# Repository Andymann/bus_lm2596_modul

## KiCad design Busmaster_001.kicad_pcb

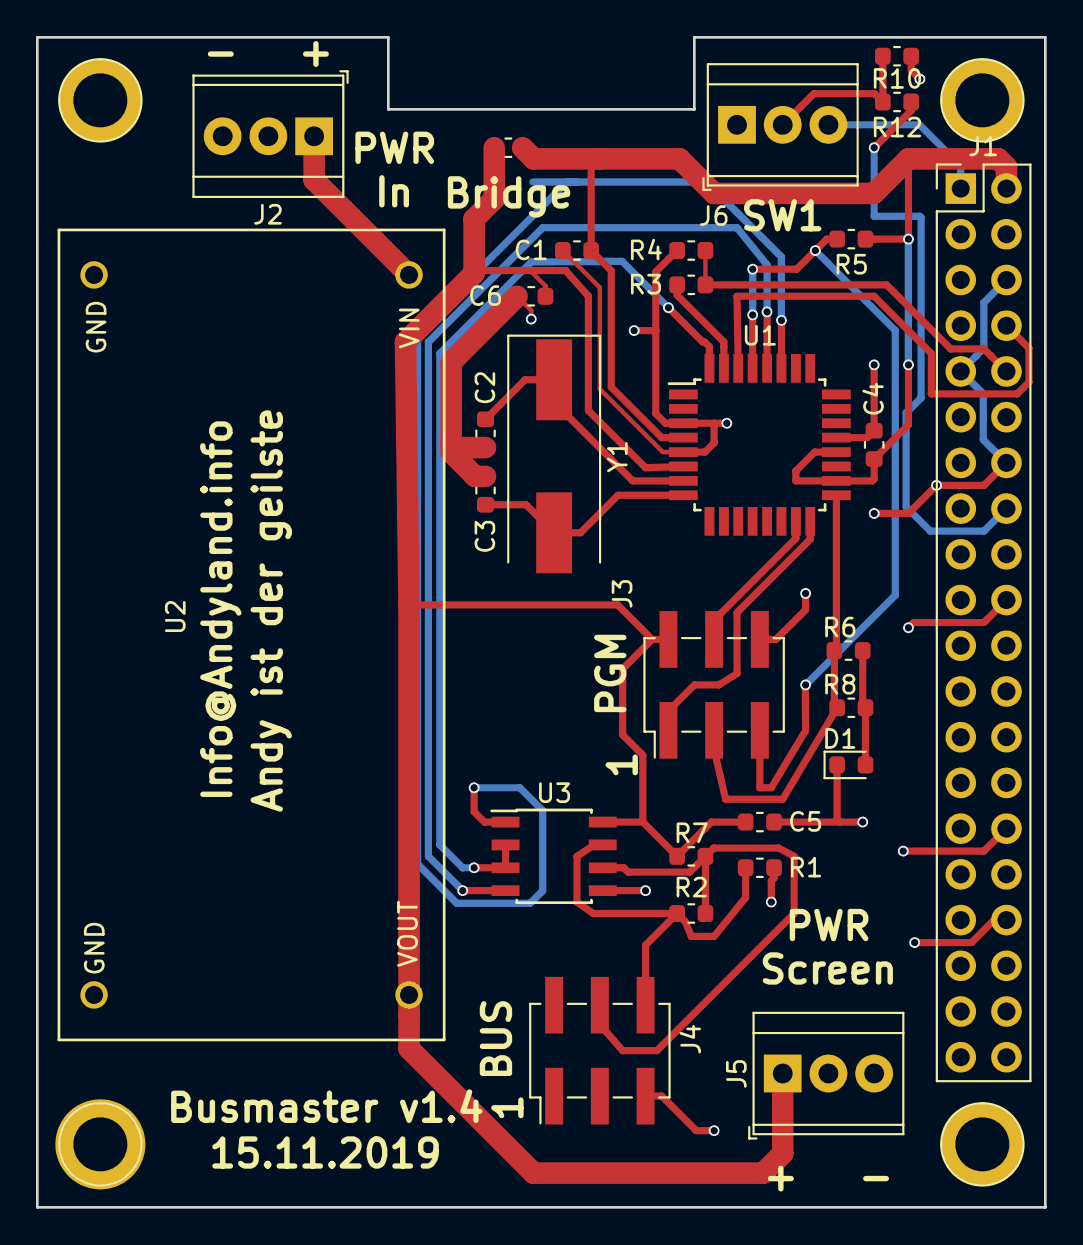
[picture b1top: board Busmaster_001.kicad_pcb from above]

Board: 2 copper layers, 56.0 x 65.0 mm, 28 parts (0 on the bottom side), 21 nets.

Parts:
C1: 100µF; C_0603_1608Metric
C2, C3: 22pF; C_0603_1608Metric
C4, C5, C6: 100nF; C_0603_1608Metric
D1: LED; LED_0603_1608Metric
J1: Conn_RPI; PinHeader_2x20_P2.54mm_Vertical
J2, J6: Conn_01x03_Female; TerminalBlock_TE_282834-3_1x03_P2.54mm_Horizontal
J3: ICSP; PinHeader_2x03_P2.54mm_Vertical_SMD
J4: CONN_BUS; PinHeader_2x03_P2.54mm_Vertical_SMD
J5: Conn_Screen; TerminalBlock_TE_282834-3_1x03_P2.54mm_Horizontal
R1, R6, R7, R8: 470; R_0603_1608Metric
R2: 100; R_0603_1608Metric
R3: 2k2; R_0603_1608Metric
R4: 3k3; R_0603_1608Metric
R5: 10k; R_0603_1608Metric
R9: 0; R_0603_1608Metric
R10: 10K; R_0603_1608Metric
R12: 1K; R_0603_1608Metric
U1: ATmega328P-AU; TQFP-32_7x7mm_P0.8mm
U2: LM2596_Module
U3: MAX485E; SOIC-8_3.9x4.9mm_P1.27mm
Y1: Crystal; Crystal_SMD_HC49-SD

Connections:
+3V3: J1.1, J6.3
+5V: C1.1, C4.2, C5.2, C6.2, J1.2, J3.2, J5.1, R5.1, R7.2, R9.1, R9.2, U1.4, U1.6, U1.18, U1.20, U2.4, U3.8
+12V: J2.1, U2.1
D2: U1.32, U3.2, U3.3
GND: C1.2, C2.1, C3.1, C4.1, C5.1, C6.1, D1.1, J1.6, J1.9, J1.14, J1.20, J1.25, J1.30, J1.34, J1.39, J2.3, J3.6, J4.5, J5.3, J6.1, R1.1, R4.2, R10.2, U1.3, U1.5, U1.21, U2.2, U2.3, U3.5
MISO: J3.1, U1.16
MOSI: J3.4, U1.15
unnamed: C2.2, U1.7, Y1.1
unnamed: C3.2, U1.8, Y1.2
unnamed: D1.2, R6.1, R8.1
unnamed: J6.2, R10.1, R12.2
unnamed: R3.1, U1.31
RESET: J3.5, R5.2, U1.29
RPI_Rx: J1.10, R3.2, R4.1
RPI_Tx: J1.8, U1.30
SCK: J3.3, R6.2, R8.2, U1.17
SCL: U1.28, U3.4
SCLOUT: J4.4, R2.2, R7.1, U3.6
SDA: U1.27, U3.1
SDAOUT: J4.6, R1.2, R2.1, U3.7
SW1: J1.16, R12.1
